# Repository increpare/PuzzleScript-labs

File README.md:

`make` shows help. Use `make desktop` for this platform, `make serve` for web preparation/serving,
and `make distro` for archive assembly. See [root build commands](docs/build-commands.md).

PuzzleScript
============

Open Source HTML5 Puzzle Game Engine

Try it out at https://www.puzzlescript.net.

The Win95-style [PuzzleScript+MIS workbench](desktop/mis/README.md) also runs as a
GUI95 desktop app. With Node 22.12+ and GNU Make, `make` shows help, `make desktop` builds the workbench and
its web version, `make install` adds the stable per-user GUI95 launcher, and
`make serve` prepares and serves only the web build. `make help` lists the engine and hardware targets.

-----

If you're interested in recompiling/modifing/hacking the engine, there is [development setup info here](DEVELOPMENT.md).  If you're just interested in learning how to use the engine/make games in it, [the documentation is here](https://www.puzzlescript.net/Documentation/documentation.html).

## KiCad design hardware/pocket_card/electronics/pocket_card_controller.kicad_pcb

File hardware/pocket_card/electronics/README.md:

# Pocket Card electronics

This directory contains the authoritative native KiCad project for the Pocket
Card controller. Engineers edit `pocket_card_controller.kicad_pro` here.

## Editing rules

Annotate every new symbol before updating the PCB. PCB updates must use the
established symbol associations so existing footprints, placement, and routing
remain attached to their intended symbols.

Custom symbols, footprints, and 3D models must use `${KIPRJMOD}`-relative paths
in the project tree:

- `symbols/` — custom schematic symbols
- `footprints.pretty/` — custom footprints
- `3dmodels/` — STEP/WRL models referenced by footprints

Machine-local or absolute asset paths are not permitted. The project-local
`fp-lib-table` and optional `sym-lib-table` reference KiCad 10 standard libraries
via `${KICAD10_FOOTPRINT_DIR}` and project-relative custom entries.

KiCad **10.0.4** or newer is required (`toolchain.json` pins major version 10
and the minimum release).

KiCad local state is not source: do not commit `.kicad_prl` files, `.lck` files,
backups, or caches.

## Validation and exports

Normal Make targets validate or export this project. They never regenerate the
schematic, component placement, or routing.

```
make pocket_card_kicad           # read-only validation (ERC, DRC, parity, mechanics)
make pocket_card_kicad_check     # same validation entry point
make pocket_card_pcb_exports     # gerbers, BOM, drill, pos, STEP, STL → case/out/pcb/
```

`make pocket_card_kicad` runs `electronics_pipeline.validation` against the
checked-in project. It is not a generator.

## Mechanical contract and locks

`mechanical_contract.json` records placement, courtyard, overlap, and keepout
rules that tie the routed board to enclosure CAD in `case/`. Validation compares
the live board against this contract.

Footprint and Edge.Cuts locks on contracted items are accident prevention — they
discourage casual KiCad drags. The contract is the review gate: if an engineer
moves a contracted feature, update `mechanical_contract.json` deliberately (and
enclosure CAD / `case/params.py` when the shell must change) before validation
passes.

`validation_waivers.json` holds the canonical ERC/DRC/parity warning policy.
Returned copies in engineer handoff ZIPs cannot waive findings; check always
uses this repository file.

## Silkscreen

Board silk defaults to **readable mode**: functional UI legends (POWER / MUTE /
connector titles + pin names) plus visible front KiCad `Reference`s. D-pad
`^V<>` glyphs are decorative and stay off.
Back-side connector refs stay hidden so they don't stamp over the generator
labels. Dense decorative art (brick wallpaper, rule corpus, brand/logo) is off
by default.

Restore decorative silk later by setting `DECORATIVE_SILK = True` in
`../case/params.py`, then:

```bash
cd hardware/pocket_card/case && .venv/bin/python -c \
  "import silk; print(silk.refresh_board_silk('../electronics/pocket_card_controller.kicad_pcb'))"
```

After toggling, regenerate silk DRC waiver digests in `validation_waivers.json`
(and the matching `_EXPECTED_WARNING_POLICY` entries) so `make pocket_card_kicad`
still passes.

## Engineer handoff

Repeated ZIP exchange with an external engineer:

```
make pocket_card_engineer_export                  # INCLUDE_BLEND=1 by default
make pocket_card_engineer_check ZIP=/absolute/path/returned.zip
make pocket_card_engineer_accept STAGED=/absolute/path/printed-stage
```

Full operator runbook: [`../README.md`](../README.md#engineer-exchange-workflow).

`pocket_card_engineer_check` stages the returned project, runs the same
validation as `pocket_card_kicad`, diffs inventories against the baseline
recorded in the handoff metadata, and writes `report.md`. Unknown or concurrent
stale baselines are not auto-merged.

After accept, run `make pocket_card_kicad` and `make pocket_card_case`, then
commit KiCad source separately from regenerated release artifacts in
`case/out/`.

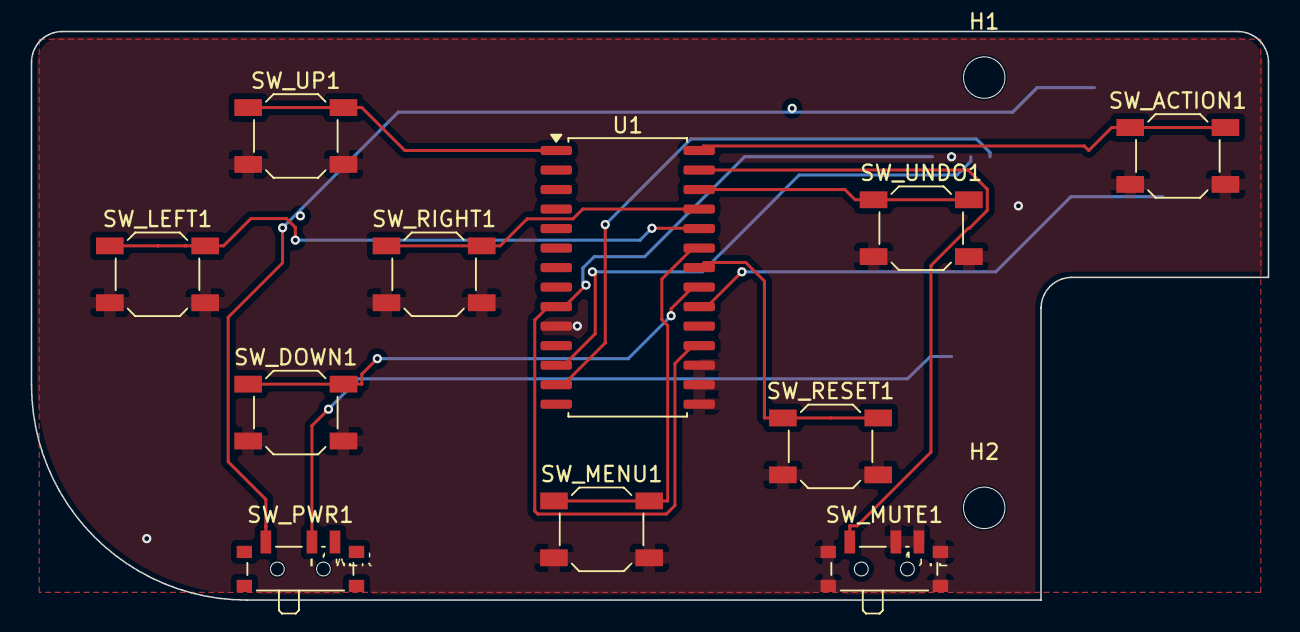
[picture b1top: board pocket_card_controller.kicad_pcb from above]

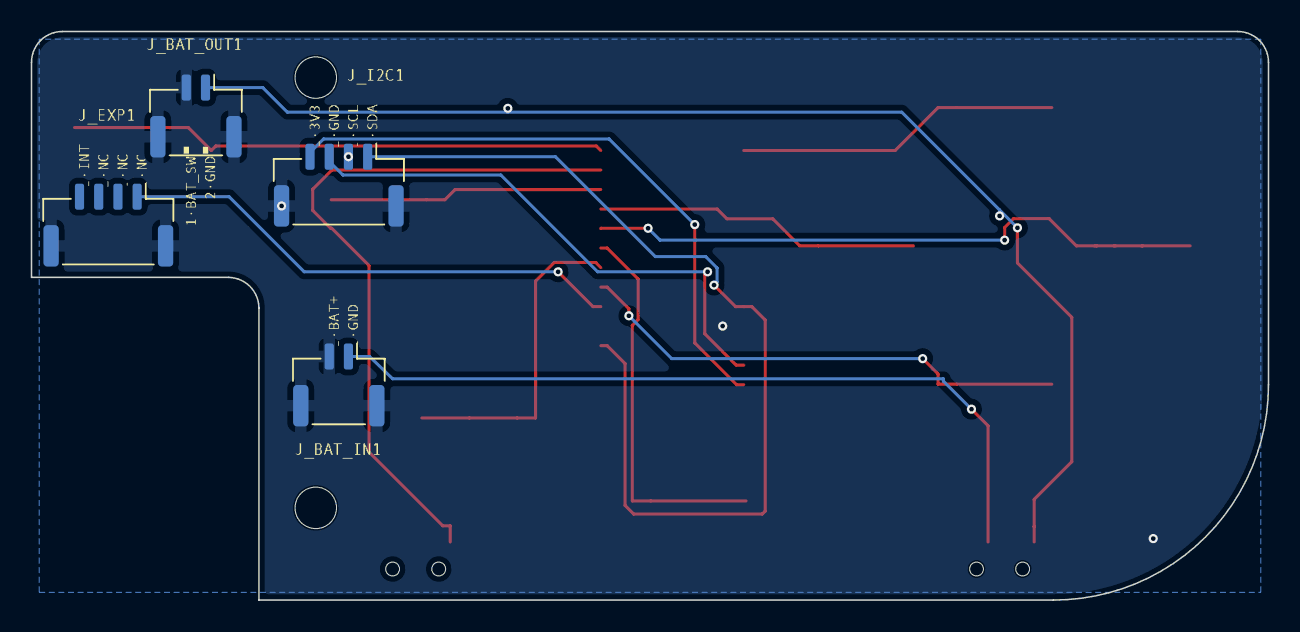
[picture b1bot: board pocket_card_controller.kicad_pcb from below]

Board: 2 copper layers, 80.5 x 37.0 mm, 17 parts (4 on the bottom side), 16 nets.

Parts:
H1, H2: MountingHole_2.7mm_M2.5
J_BAT_IN1: JST_GH_SM02B-GHS-TB_1x02-1MP_P1.25mm_Horizontal
J_BAT_OUT1: JST_GH_SM02B-GHS-TB_1x02-1MP_P1.25mm_Horizontal
J_EXP1: JST_GH_SM04B-GHS-TB_1x04-1MP_P1.25mm_Horizontal
J_I2C1: JST_GH_SM04B-GHS-TB_1x04-1MP_P1.25mm_Horizontal
SW_ACTION1: SW_SPST_SKQG_WithStem
SW_DOWN1: SW_SPST_SKQG_WithStem
SW_LEFT1: SW_SPST_SKQG_WithStem
SW_MENU1: SW_SPST_SKQG_WithStem
SW_MUTE1: SW_SPDT_PCM12
SW_PWR1: SW_SPDT_PCM12
SW_RESET1: SW_SPST_SKQG_WithStem
SW_RIGHT1: SW_SPST_SKQG_WithStem
SW_UNDO1: SW_SPST_SKQG_WithStem
SW_UP1: SW_SPST_SKQG_WithStem
U1: SOIC-28W_7.5x17.9mm_P1.27mm

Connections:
+3V3: J_I2C1.1, U1.9, U1.18
BAT_P: J_BAT_IN1.1, SW_PWR1.2
BAT_SW: J_BAT_OUT1.1, SW_PWR1.1
GND: J_BAT_IN1.2, J_BAT_IN1.MP, J_BAT_OUT1.2, J_BAT_OUT1.MP, J_EXP1.MP, J_I2C1.2, J_I2C1.MP, SW_ACTION1.2, SW_DOWN1.2, SW_LEFT1.2, SW_MENU1.2, SW_MUTE1.2, SW_MUTE1.3, SW_RESET1.2, SW_RIGHT1.2, SW_UNDO1.2, SW_UP1.2, U1.10, U1.15, U1.16, U1.17
INT: J_EXP1.1, U1.20
SCL: J_I2C1.3, U1.12
SDA: J_I2C1.4, U1.13
SIG_ACTION: SW_ACTION1.1, U1.28
SIG_DOWN: SW_DOWN1.1, U1.21
SIG_LEFT: SW_LEFT1.1, U1.24
SIG_MENU: SW_MENU1.1, U1.23
SIG_MUTE: SW_MUTE1.1, U1.27
SIG_RESET: SW_RESET1.1, U1.22
SIG_RIGHT: SW_RIGHT1.1, U1.25
SIG_UNDO: SW_UNDO1.1, U1.26
SIG_UP: SW_UP1.1, U1.1

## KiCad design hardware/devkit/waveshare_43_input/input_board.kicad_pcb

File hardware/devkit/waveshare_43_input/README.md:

# Waveshare 4.3″ Input Daughterboard

Eight clicky tact switches in the **PuzzleScript card control layout**, wired to the GPIO map used by `firmware/esp32p4` breadboard bring-up. Connects to the [Waveshare ESP32-P4-WIFI6-Touch-LCD-4.3](https://docs.waveshare.com/ESP32-P4-WIFI6-Touch-LCD-4.3) **40-pin expansion header** via a 10-wire dupont harness.

## Generate

```bash
make handheld_devkit_input_kicad
```

Open `input_board.kicad_pro` in KiCad 8. Review DRC, then order from JLCPCB (2-layer, 1.6 mm default is fine).

## Layout (mm, card front coordinates)

| Ref | Control | Center (X, Y) | GPIO |
|-----|---------|---------------|------|
| SW1 | D-pad Up | 22, 78.25 | 28 |
| SW2 | D-pad Down | 22, 95.75 | 29 |
| SW3 | D-pad Left | 13.25, 87 | 30 |
| SW4 | D-pad Right | 30.75, 87 | 31 |
| SW5 | Action | 89, 83 | 32 |
| SW6 | Undo | 75, 96 | 34 |
| SW7 | Restart | 92, 102 | 35 |
| SW8 | Menu | 58, 101 | 49 |

Positions come from `tools/handheld_blockout/blockout.js` (`spacing: 17.5` mm D-pad).

## J1 → Waveshare 40-pin

**J1** is a **1×10 2.54 mm male header** on the daughterboard. Run dupont wires to the expansion header on the **same GPIO numbers** you used on breadboard:

| J1 pin | Signal | Wire to |
|--------|--------|---------|
| 1 | GND | GND on expansion header |
| 2 | GPIO28 | D-pad Up |
| 3 | GPIO29 | D-pad Down |
| 4 | GPIO30 | D-pad Left |
| 5 | GPIO31 | D-pad Right |
| 6 | GPIO32 | Action |
| 7 | GPIO34 | Undo |
| 8 | GPIO35 | Restart |
| 9 | GPIO49 | Menu |
| 10 | GND | GND |

Do **not** use GPIO 7/8 (I2C codec), 9–13 (audio), or 53 (amp enable) on the Waveshare 4.3 board — see `gpio_map.json`.

The 40-pin header follows a Raspberry Pi HAT-style pinout; use a multimeter or the Waveshare schematic PDF to find which physical header pins are GND and your chosen GPIOs. Your breadboard wiring is the ground truth if it already works.

## BOM (JLC)

| Part | LCSC | Qty |
|------|------|-----|
| TL3315NF160Q tact | C2886877 | 8 |
| 1×10 pin header 2.54 mm | C492421 | 1 |

See `bom_jlc.csv`.

## Firmware

Default `board_buttons.cpp` pin map matches this board (GPIO 28–32, 34, 35, 49). Rebuild with `make handheld_p4_probe_build` after any wiring change.

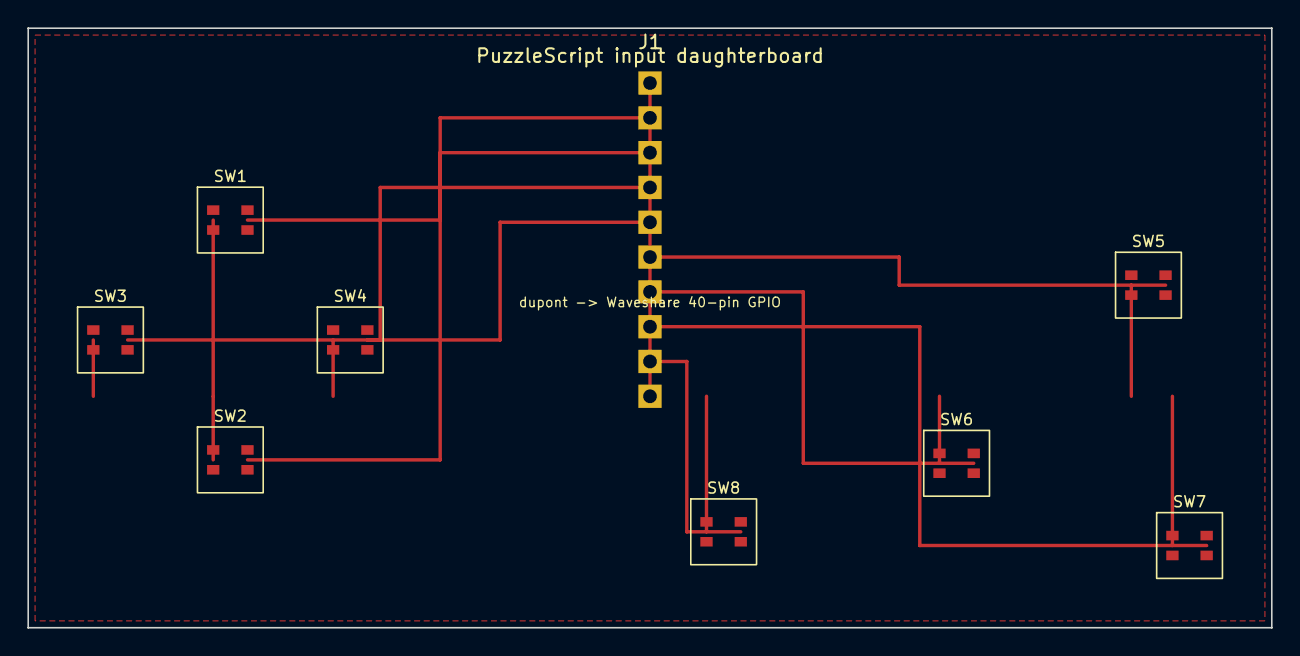
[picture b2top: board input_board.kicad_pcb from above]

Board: 2 copper layers, 90.8 x 43.8 mm, 9 parts (0 on the bottom side), 9 nets.

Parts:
J1: To_Waveshare_40pin; Connector_PinHeader_1x10_P2.54mm_Vertical
SW1: UP; TL3315NF160Q
SW2: DOWN; TL3315NF160Q
SW3: LEFT; TL3315NF160Q
SW4: RIGHT; TL3315NF160Q
SW5: ACTION; TL3315NF160Q
SW6: UNDO; TL3315NF160Q
SW7: RESTART; TL3315NF160Q
SW8: MENU; TL3315NF160Q

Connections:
GND: J1.1, J1.10, SW1.1, SW1.2, SW2.1, SW2.2, SW3.1, SW3.2, SW4.1, SW4.2, SW5.1, SW5.2, SW6.1, SW6.2, SW7.1, SW7.2, SW8.1, SW8.2
GPIO28_UP: J1.2, SW1.3, SW1.4
GPIO29_DOWN: J1.3, SW2.3, SW2.4
GPIO30_LEFT: J1.4, SW3.3, SW3.4
GPIO31_RIGHT: J1.5, SW4.3, SW4.4
GPIO32_ACTION: J1.6, SW5.3, SW5.4
GPIO34_UNDO: J1.7, SW6.3, SW6.4
GPIO35_RESTART: J1.8, SW7.3, SW7.4
GPIO49_MENU: J1.9, SW8.3, SW8.4

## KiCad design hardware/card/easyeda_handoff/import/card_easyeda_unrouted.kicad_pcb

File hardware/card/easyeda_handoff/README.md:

# EasyEDA Handoff - PuzzleScript Card

This package is for manual PCB routing in EasyEDA Pro. It ships a full KiCad project
with JLC/LCSC part numbers, EasyEDA footprint names, schematic sheets, placement anchors,
and an unrouted PCB.

**Important:** EasyEDA Pro's KiCad importer brings in placement, nets, and custom fields,
but it does **not** auto-link parts to EasyEDA's LCSC library. That linking only happens
when you place parts from EasyEDA's own library panel. The `LCSC` / `MPN` fields here are
for procurement (JLCPCB BOM export from KiCad) and as a lookup table while you associate
parts in EasyEDA — not for automatic import-time matching.

## Start Here (EasyEDA Pro)

1. **Import the full KiCad project**: `import/card.kicad_pro` (File → Import → KiCad).
2. **Associate LCSC parts** (required, not automatic):
   - Open **Left panel → Device Standardization** for flagged mismatches.
   - Or **Tools → Device Manager**: select a component, choose **Assign LCSC Part**,
     and search by the `LCSC` column from `import/bom_jlc.csv` (e.g. `C2765186`), not
     by the generic KiCad value string.
   - There are **29 unique LCSC parts** for 48 designators — group identical values in
     Device Manager so each LCSC number only needs to be assigned once per part type.
3. Cross-check `import/bom_jlc.csv` and `import/schematic/jlc_catalog.json`.
4. Keep `mechanical/layout.svg` open while verifying footprint placement.
5. Route manually in this order: DSI, USB, power, storage, then low-speed controls/audio/haptics/LEDs.

### Skip EasyEDA association entirely?

If the goal is JLCPCB assembly rather than EasyEDA routing, you can stay in KiCad:
pull real symbols/footprints with [easyeda2kicad](https://github.com/uPesy/easyeda2kicad.py)
using the LCSC numbers in `bom_jlc.csv`, route in KiCad, and order with the JLCPCB
Fabrication Toolkit. The LCSC fields are already in the right shape for that path.

## JLC Catalog Coverage

- Locked parts: 27
- Candidate parts (gate still open): 20
- Open / off-board: 1

Re-check LCSC stock and assembly tier immediately before ordering.

## Current Generated Route Reference

| Family | Status | Generated routes | Airwires | Gate |
|---|---:|---:|---:|---|
| Low-speed | routed-first-pass | 37 | 0 |  |
| DSI | routed-assumption-gated | 6 | 0 | GATE-DSI-FFC-CONTACT |
| USB | routed-first-pass-review | 4 | 0 |  |
| Power | routed-first-pass-review | 22 | 0 |  |
| Storage | routed-first-pass-gated | 4 | 0 | GATE-MICROSD-FOOTPRINT |

The generated reference currently reports 73 routed traces and 0 airwires.
Treat those traces as connectivity proof only, not a manufacturable layout.

## Key Gates

- `GATE-DSI-FFC-CONTACT`: do not finalize DSI routing until the real FFC contact side, latch side, cable exit, and pin 1 are confirmed.
- `GATE-MICROSD-FOOTPRINT`: pick the actual internal service socket footprint before final SD routing.
- `GATE-POWER-SLIDE-SLOT`: check switch travel/slot and OFF/ON orientation in the shell.
- `GATE-BATTERY-SAMPLE`: measure protected 403048-class cells before final battery connector placement.
- `GATE-ESP32-P4-REF-CAPTURE`: verify crystal load caps, flash voltage domain, and P4 DC-DC inductor against Espressif reference.

## Contents

- `import/`: KiCad project, JLC BOM, catalog JSON, schematic sheets, netlist.
- `mechanical/`: layout JSON/SVG exported from the blockout tool.
- `reference/`: generated preview HTML/SVG/JSON and routed-reference KiCad PCB.
- `docs/`: gate, DSI, component, and pin-budget notes.

## Fabrication Warning

Do not order from this package without human routing review, DRC/ERC, footprint verification,
JLC/LCSC availability review, and a mechanical check against the case.

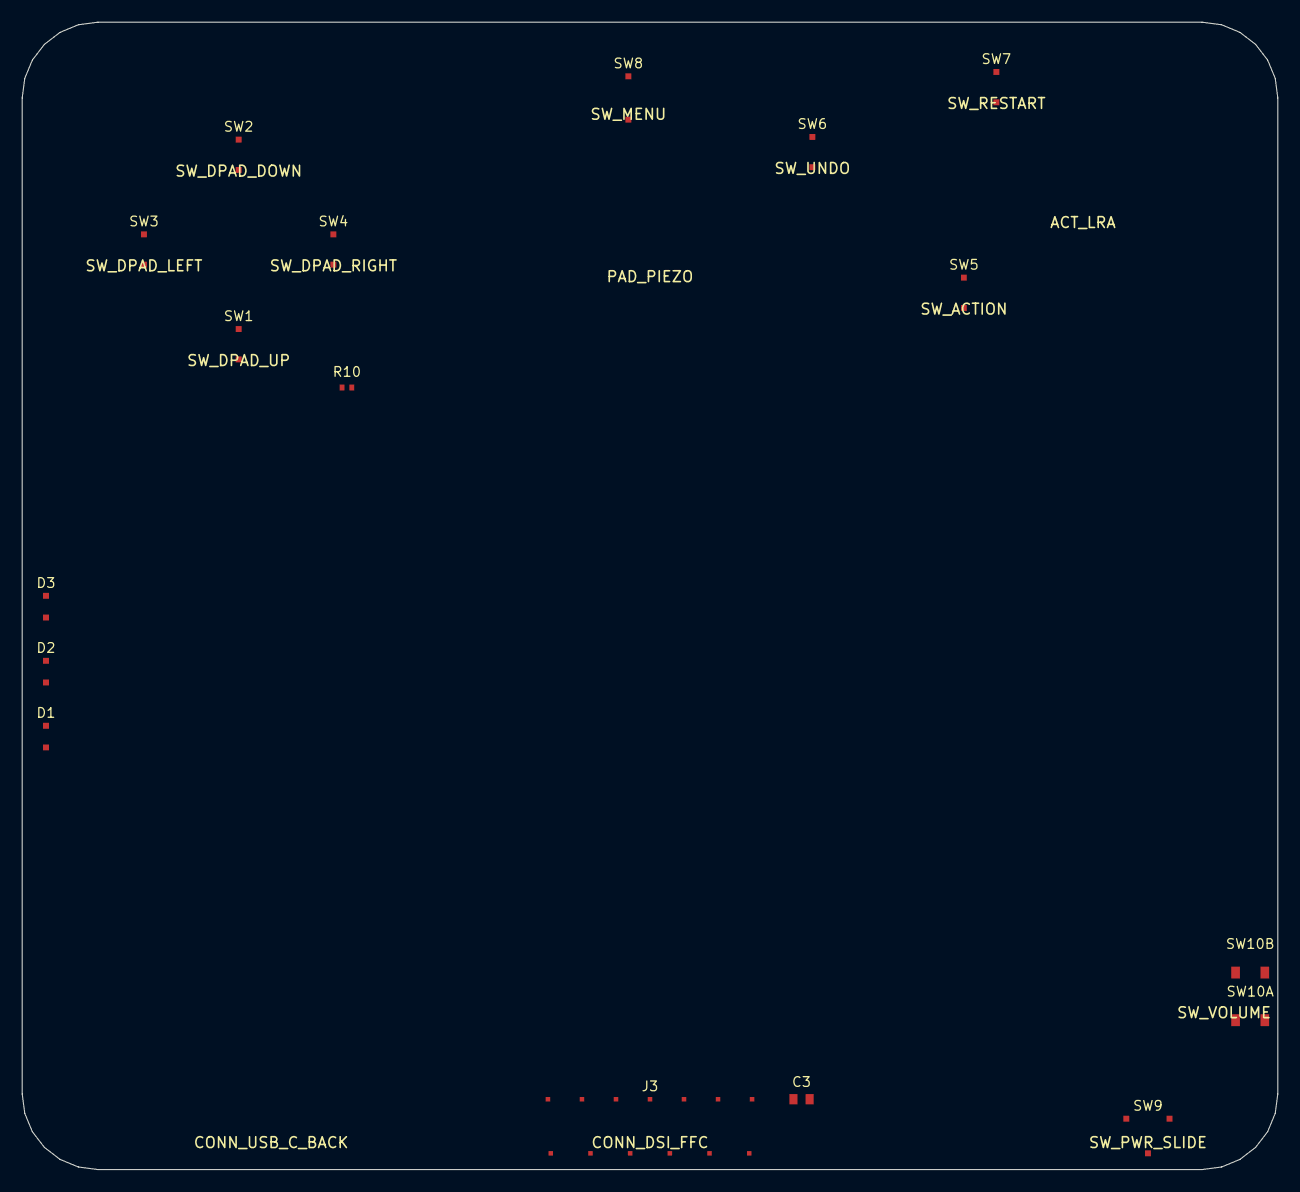
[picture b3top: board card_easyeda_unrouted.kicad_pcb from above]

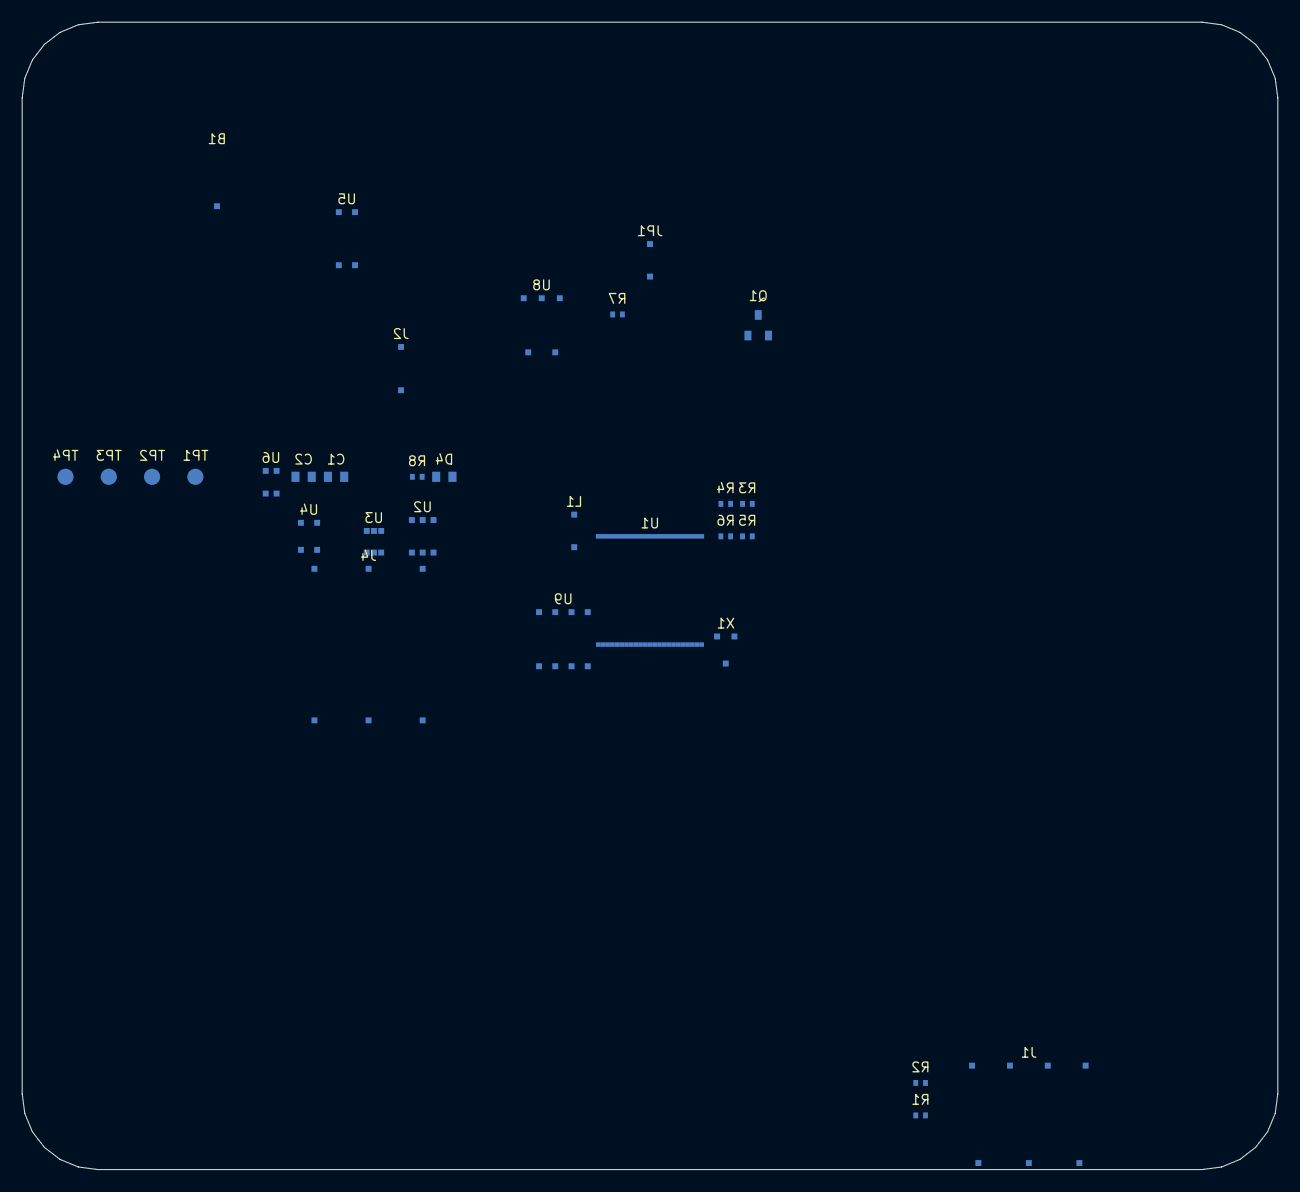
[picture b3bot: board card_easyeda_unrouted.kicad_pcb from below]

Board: 4 copper layers, 116.0 x 106.0 mm, 48 parts (31 on the bottom side), 58 nets, no tracks yet.

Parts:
B1: Coin-LRA-10mm; VIBRATING-MOTOR-SMD_WELDING
C1, C2, C3: 10u; C0603
D1: LED-R; LED0603-RD
D2: LED-G; LED0603-GN
D3: LED-B; LED0603-FD_BLUE
D4: LED-CHG; LED0603-RD
J1: HRO-TYPE-C-31-M-12; USB-C-SMD_TYPE-C-16PIN-2MD-073
J2: 1S-Pouch-403048; CONN-SMD_SM02B-SRSS-TB
J3: FFC-15-1.0-FH12-class; FPC-SMD_FH12-15S-0.5SH-55
J4: microSD; TF-015
JP1: PiezoPads; TestPoint_Pad_D1.5mm
L1: 2.2uH; IND-SMD_L4.0-W4.0_HPC4018BM
Q1: NPN; SOT-23_L2.9-W1.6-P1.90-LS2.8-BR
R1, R2: 5.1k; R0402
R3, R4: 4.7k; R0402
R5, R6, R10: 10k; R0402
R7: 0R; R0402
R8: 1k; R0402
SW1, SW2, SW3, SW4: TL3315NF160Q-class; SW-SMD_4P-L4.5-W4.5-P3.00-LS4.5-TL
SW5, SW6, SW7, SW8: KMR211NG; SW-SMD_4P-L6.0-W6.0-P4.50-LS6.5-TL
SW9: SlideSwitch-SPDT-JS102000-class; SW-SMD_6P-L7.0-W3.5-P1.27-LS4.5-TL
SW10A, SW10B: EVP-AKE31A; SW-SMD_2P-L3.9-W2.9-P1.90-LS2.8-BR
TP1: UART_TX; TestPoint_Pad_D1.5mm
TP2: UART_RX; TestPoint_Pad_D1.5mm
TP3: BOOT; TestPoint_Pad_D1.5mm
TP4: EN; TestPoint_Pad_D1.5mm
U1: ESP32-P4NRW32X; QFN-104_L10.0-W10.0-P0.35-TL-EP7.5
U2: BQ24075RGTR; QFN-16_L3.0-W3.0-P0.50-TL-EP1.7
U3: MAX17048G+T10; TDFN-8_L2.0-W2.0-P0.50-BL-EP1.2
U4: TPS63070; VQFN-HR-15_L3.0-W2.5-P0.50-BL_TPS63070RNMR
U5: DRV2605LDGS; VSSOP-10_L3.0-W3.0-P0.50-LS4.9-BL
U6: TPS22919DCK; SC-70-6_L2.2-W1.3-P0.65-LS2.1-BR
U8: PiezoHBridge-DNP; W-QFN2020-12_L2.0-W2.0-P0.40-TL-EP0.9
U9: QSPI-NOR-32MB; WSON-8_L8.0-W6.10-P1.27-BL-EP
X1: 40MHz-crystal; SMD3225-4P

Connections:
+3V3: C1.1, C2.1, J4.VDD, R3.1, R4.1, R5.1, R6.1, U1.VDD_3V3, U3.VCC, U4.VOUT, U5.VDD, U6.IN, U8.VDD, U9.VCC
+3V3_PANEL: C3.1, J3.14, J3.15, U6.OUT
BAT+: J2.1, U2.BAT, U3.CELL
BOOT: TP3.1, U1.GPIO35
BOOT_EN: R6.2, U1.GPIO36
CHG_LED: D4.A, R8.2
CHG_STAT: D4.K, U2.CHG
DCDC_FB: L1.2, U1.FB_DCDC
DCDC_L: L1.1, U1.VDD_DCDC
DSI_CLK_N: J3.5, U1.DSI_CLKN
DSI_CLK_P: J3.6, U1.DSI_CLKP
DSI_D0_N: J3.8, U1.DSI_DATAN0
DSI_D0_P: J3.9, U1.DSI_DATAP0
DSI_D1_N: J3.2, U1.DSI_DATAN1
DSI_D1_P: J3.3, U1.DSI_DATAP1
ESP_EN: R5.2, TP4.1, U1.EN
FLASH_CLK: U1.SPI_CLK, U9.CLK
FLASH_CS: U1.SPI_CS, U9.CS
FLASH_D0: U1.SPI_D0, U9.D0
FLASH_D1: U1.SPI_D1, U9.D1
FLASH_D2: U1.SPI_D2, U9.D2
FLASH_D3: U1.SPI_D3, U9.D3
GAUGE_ALERT: U1.GPIO45, U3.ALRT
GND: B1.2, C1.2, C2.2, C3.2, D1.K, D2.K, D3.K, J1.GND, J1.SHIELD, J2.2, J3.1, J3.4, J3.7, J3.10, J3.13, J4.VSS, Q1.E, R1.2, R2.2, R7.2, SW1.2, SW2.2, SW3.2, SW4.2, SW5.2, SW6.2, SW7.2, SW8.2, SW9.B, SW10A.2, SW10B.2, U1.GND, U2.GND, U2.SYSOFF, U3.GND, U4.GND, U5.GND, U6.GND, U8.GND, U9.GND, X1.GND
I2C_SCL: R4.2, U1.GPIO27, U3.SCL, U5.SCL
I2C_SDA: R3.2, U1.GPIO26, U3.SDA, U5.SDA
LED_B: D3.A, U1.GPIO44
LED_G: D2.A, U1.GPIO43
LED_R: D1.A, U1.GPIO42
PANEL_EN: U1.GPIO11, U6.ON
PIEZO_OUT: JP1.1, Q1.C, U8.OUTP
PIEZO_PWM: Q1.B, U1.GPIO41, U8.IN
PIEZO_RET: JP1.2, R7.1, U8.OUTN
PWR_EN: SW9.C, U4.EN
SD_SPI_CLK: J4.CLK, U1.GPIO47
SD_SPI_CS: J4.CS, U1.GPIO46
SD_SPI_MISO: J4.DO, U1.GPIO49
SD_SPI_MOSI: J4.DI, U1.GPIO48
SW_ACTION: SW5.1, U1.GPIO10
SW_DPAD_DOWN: SW2.1, U1.GPIO9
SW_DPAD_LEFT: SW3.1, U1.GPIO30
SW_DPAD_RIGHT: SW4.1, U1.GPIO31
SW_DPAD_UP: R10.1, SW1.1, U1.GPIO28
SW_MENU: SW8.1, U1.GPIO37
SW_RESTART: SW7.1, U1.GPIO34
SW_UNDO: SW6.1, U1.GPIO33
SYS: SW9.A, U2.OUT, U4.VIN
UART_RX: TP2.1, U1.GPIO51
UART_TX: TP1.1, U1.GPIO50
USB_CC1: J1.CC1, R1.1
USB_CC2: J1.CC2, R2.1
USB_DM: J1.D-, U1.USB_DM
USB_DP: J1.D+, U1.USB_DP
VBUS_IN: J1.VBUS, R8.1, U2.IN
VOL_DOWN: SW10B.1, U1.GPIO40
VOL_UP: SW10A.1, U1.GPIO39
XTAL_IN: U1.XTAL_P, X1.1
XTAL_OUT: U1.XTAL_N, X1.2
